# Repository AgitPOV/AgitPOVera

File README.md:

# AgitPOVera

* "Circuit" was designed with Eagle.
* "Code" is made for Arduino to be run on the "Agit POVera (ATmega168,internal 8Mhz)" hardware (see next bullet point).
** "Code\hardware" : please put the "hardware" folder in your Arduino sketchbook.
* "Software" is made for Processing.

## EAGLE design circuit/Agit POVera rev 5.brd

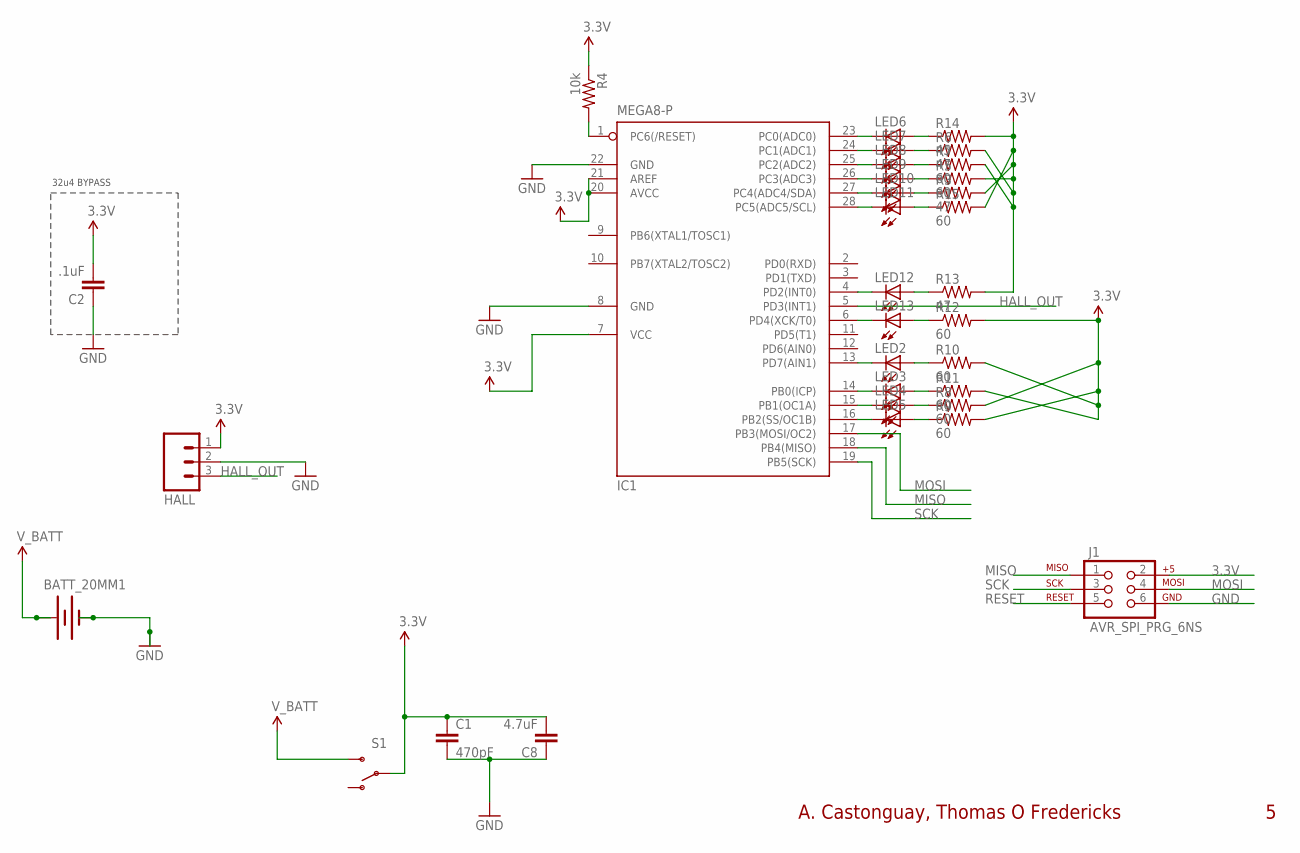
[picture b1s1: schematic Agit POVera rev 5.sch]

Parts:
BATT_20MM1: BATTERIE
C1: 470pF; CAP-PTH-SMALLEZ
C2: .1uF; CAP-PTH-SMALLEZ
C8: 4.7uF; CAP-PTH-SMALLEZ
HALL: M03PTH; 1X03
IC1: MEGA8-P; DIL28-3
J1: AVR_SPI_PRG_6NS; 2X3-NS
LED2, LED3, LED4, LED5, LED6, LED7, LED8, LED9, LED10, LED11, LED12, LED13: LED5MM
R3, R6, R13: 47; 0204/7
R4: 10k; 0204/7
R5, R7, R8, R9, R10, R11, R12, R15: 60; 0204/7
R14: 45; 0204/7
S1: SWITCH-SPDTPTH; SWITCH-SPDT

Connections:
3.3V: C1.1, C2.2, C8.2, HALL.1, IC1.7 (VCC), IC1.20 (AVCC), IC1.21 (AREF), J1.2, R3.2, R4.1, R5.2, R6.2, R7.2, R8.2, R9.2, R10.2, R11.2, R12.2, R13.2, R14.2, R15.2, S1.2
GND: BATT_20MM1.2 (-), C1.2, C2.1, C8.1, HALL.2, IC1.8 (GND), IC1.22 (GND), J1.6
HALL_OUT: HALL.3, IC1.5 (PD3(INT1))
LED2: IC1.13 (PD7(AIN1)), LED2.K (C)
LED3: IC1.14 (PB0(ICP)), LED3.K (C)
LED4: IC1.15 (PB1(OC1A)), LED4.K (C)
LED5: IC1.16 (PB2(SS/OC1B)), LED5.K (C)
LED6: IC1.23 (PC0(ADC0)), LED6.K (C)
LED7: IC1.24 (PC1(ADC1)), LED7.K (C)
LED8: IC1.25 (PC2(ADC2)), LED8.K (C)
LED9: IC1.26 (PC3(ADC3)), LED9.K (C)
LED10: IC1.27 (PC4(ADC4/SDA)), LED10.K (C)
LED11: IC1.28 (PC5(ADC5/SCL)), LED11.K (C)
LED12: IC1.4 (PD2(INT0)), LED12.K (C)
LED13: IC1.6 (PD4(XCK/T0)), LED13.K (C)
MISO: IC1.18 (PB4(MISO)), J1.1
MOSI: IC1.17 (PB3(MOSI/OC2)), J1.4
unnamed: LED7.A, R6.1
unnamed: LED12.A, R13.1
unnamed: LED13.A, R12.1
unnamed: LED3.A, R11.1
unnamed: LED2.A, R10.1
unnamed: LED5.A, R9.1
unnamed: LED4.A, R8.1
unnamed: LED10.A, R3.1
unnamed: LED11.A, R15.1
unnamed: LED6.A, R14.1
R7: LED8.A, R7.1
R9: LED9.A, R5.1
RESET: IC1.1 (PC6(/RESET)), J1.5, R4.2
SCK: IC1.19 (PB5(SCK)), J1.3
V_BATT: BATT_20MM1.1 (+), S1.3 (S)

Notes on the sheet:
32u4 BYPASS
A. Castonguay, Thomas O Fredericks

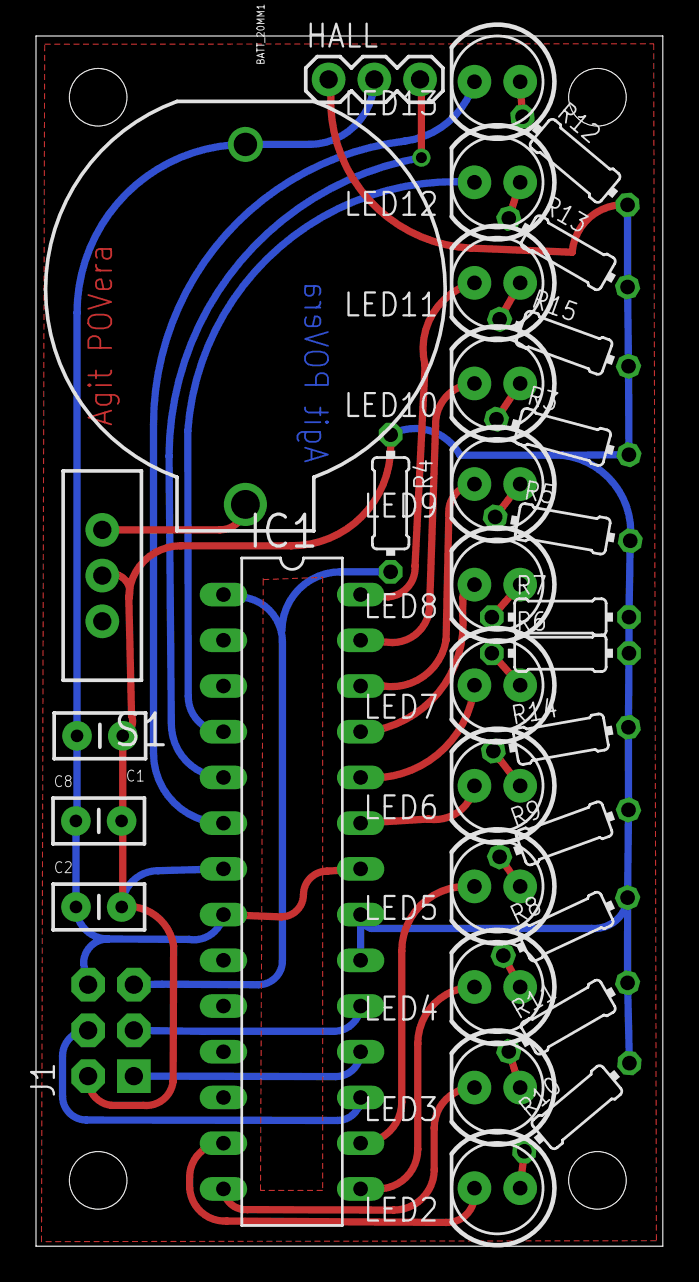
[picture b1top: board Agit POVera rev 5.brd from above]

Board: 2 copper layers, 34.8 x 67.2 mm, 33 parts (0 on the bottom side), 32 nets.

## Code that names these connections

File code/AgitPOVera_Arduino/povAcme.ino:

/*
 * AgitPOV
 * 12-LED POV for Arduino
 * Can display a led array
 * Thomas O Fredericks
 * (c) 2014
 
 VERSION
 ===========================
 0.13:
 POV display should restart if retriggered
 
 0.12:
 Moved a lot of code to povAcme.ino.
 Added an option for continuous display.
 Added an option to set the column width.
 
 0.11:
 Replaced povWaitAndDisplay with povDisplayCheck.
 
 0.1:
 Initial release.
 
 *
 * This program is free software: you can redistribute it and/or modify
 * it under the terms of the GNU General Public License as published by
 * the Free Software Foundation, either version 3 of the License, or
 * (at your option) any later version.
 *
 * This program is distributed in the hope that it will be useful,
 * but WITHOUT ANY WARRANTY; without even the implied warranty of
 * MERCHANTABILITY or FITNESS FOR A PARTICULAR PURPOSE.  See the
 * GNU General Public License for more details.
 *
 * You should have received a copy of the GNU General Public License
 * along with this program.  If not, see <http://www.gnu.org/licenses/>.
 */

/* DEFINES
=========================== */

// POSSIBLE BOARDS
#define COYOTE 1
#define POVERA 2

// ACTUAL BOARD
#define BOARD POVERA

//#define COYOTE_SLOW_DEBUG

/*
                                                                                                                          
   _____                  _       
  / ____|                | |      
 | |     ___  _   _  ___ | |_ ___ 
 | |    / _ \| | | |/ _ \| __/ _ \
 | |___| (_) | |_| | (_) | ||  __/
  \_____\___/ \__, |\___/ \__\___|
               __/ |              
              |___/               


COYOTE POV PIN CONFIGURTATION
==========================
LED ATMEGA168 ARDUINO PIN
13 PD0 0
12 PD1 1
11 PC1 A1
10 PC2 A2
9 PC3 A3
8 PC5 A5
7 PC4 A4
6 PC0 A0
5 PB0 8
4 PD7 7
3 PB2 10
2 PB1 9
PORT D MASK : 0x83 B10000011
PORT B MASK : 0x07 B00000111
PORT C MASK : 0x3F B00111111

ARDUINO
ATMEGA168 PIN INTERRUPT
HALL PD3 3 1

______________________   ____                   
\______   \_____  \   \ /   /________________   
 |     ___//   |   \   Y   // __ \_  __ \__  \  
 |    |   /    |    \     /\  ___/|  | \// __ \_
 |____|   \_______  /\___/  \___  >__|  (____  /
                  \/            \/           \/ 


POVERA PIN CONFIGURTATION
==========================
LED ATMEGA168 ARDUINO PIN
13  PD4    4
12  PD2    2
11  PC5    A5
10  PC4    A4
9   PC3    A3
8   PC2    A2
7   PC1    A1
6   PC0    A0  
5   PB2    10
4   PB1    9
3   PB0    8
2   PD7    7
PORT D MASK : 0x83 B10000011
PORT B MASK : 0x07 B00000111
PORT C MASK : 0x3F B00111111

ARDUINO
ATMEGA168 PIN INTERRUPT
HALL PD3 3 1
*/

#if BOARD == COYOTE

unsigned char povLedPins[]={
  9,10,7,8,A0,A4,A5,A3,A2,A1,1,0};
#define HALL_INTERRUPT 1
#define HALL_PIN 3

#elif BOARD == POVERA

unsigned char povLedPins[]={
  7,8,9,10,A0,A1,A2,A3,A4,A5,2,4};
#define HALL_INTERRUPT 1
#define HALL_PIN 3

#endif



volatile boolean povDoIt = false;


int * _povArray;
int _povArraySize;


unsigned long povIntervalColumns = 3300;

int _povColumnWidth = 1;

volatile unsigned long povInterval = 1100;
volatile unsigned long povTimeStamp;

volatile int _povArrayIndex = 0;



void povSetup() {

  // Set up pin 0 - 12 as OUTPUT.
  for (unsigned char k=0;k<12;k++) {
    pinMode(povLedPins[k],OUTPUT);
    //digitalWrite(povLedPins[k],HIGH);
  }

  // initialize HALL with interrupt
  attachInterrupt(HALL_INTERRUPT, hallInterrupt, FALLING);
  pinMode(HALL_PIN, INPUT);
  digitalWrite(HALL_PIN, HIGH);


}


void povSetArray ( int* a, int s) {
  _povArray = a;
  _povArraySize = s;
}

void povSetWidth(int w) {
  
  _povColumnWidth = w;
}



  // TURN OFF ALL LEDS
  // ====================================
void povTurnOffAllLeds() { 
  
  for (unsigned char k=0;k<12;k++) {
    digitalWrite(povLedPins[k],HIGH);
  }
  
}

  // 2s FADE OUT ANIMATION  
  // ================================
void povFadeOutAnimation() {
  unsigned long timeStamp = millis();
  unsigned long microTimeStamp = micros();
  while ( (millis() - timeStamp) < 2000) {

    unsigned long lapsed = (micros() - microTimeStamp); // 0-2000000 

    unsigned long dim = lapsed / 200; // 0-10000
    unsigned long frame = lapsed % 10000; //0-10000

      if ( frame >= dim ) {
      for ( int i=0; i < 12 ; i++ ) digitalWrite( povLedPins[i],  LOW ); //ON
    } 
    else {
      for ( int i=0; i < 12 ; i++ ) digitalWrite( povLedPins[i],  HIGH ); //OFF
    }
  }  
}


void povDisplay(boolean wait) { 
  
  if ( wait ) {
    if ( povDoIt == false ) return;
  }
  povDoIt = false;

  
   //povIntervalColumns = povIntervalColumns;
  
  _povArrayIndex = _povArraySize-1;
  while ( _povArrayIndex >= 0 ) {
    int b = _povArray[_povArrayIndex];
     _povArrayIndex--;
    
    for (int k=0; k<12; k++) digitalWrite(povLedPins[k], bitRead(~b,k)); 
    
    #ifdef COYOTE_SLOW_DEBUG
      delay(100);
    #else
      delayMicroseconds(povIntervalColumns); //delayMicroseconds(POV_US_BETWEEN_COLUMNS);
    #endif
    
   
  }


 povTurnOffAllLeds();
  
}



void hallInterrupt() {

  povDoIt = true;
  // Restart
  _povArrayIndex = _povArraySize-1;
  povInterval = max((millis() - povTimeStamp),2)-1;
  povTimeStamp = millis() ;
  povIntervalColumns = povInterval  * _povColumnWidth ; 

}

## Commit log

2015-02-19 Original files
2015-02-19 Removed design folder
2015-02-19 First BOM
2015-02-19 No idea
2015-02-24 Updated LEDs in BOM
2015-02-24 Added build guide
2015-02-24 Added code and software from Coyote
2015-02-25 Updated Arduino Code for POVera
2015-02-25 Described contents of folder
2015-02-26 Added hardware definitions for Arduino
2015-02-26 Updated descriptions of folders
2015-03-16 Fixed the code where the interval was not updating
2015-05-06 Updated hardware so it works with Arduino 1.6
2015-05-13 Changes for rev 5
    Everything new is under ‘circuit’ :
    The build guide is updated;
    Removed the extra parts in the BOM;
    Added the new version of the .brd, .sch and the gerbers for people
    wanting to print more from board houses.

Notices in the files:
parts and their libraries:
SparkFun-Connectors: Licensing: CC v3.0 Share-Alike You are welcome to use this library for commercial purposes.
User-Submitted: Licensing: Creative Commons ShareAlike 4.0 International - https://creativecommons.org/licenses/by-sa/4.0
SparkFun-Aesthetics: Released under the Creative Commons
